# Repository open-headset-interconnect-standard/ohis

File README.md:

# Open-Headset-Interconnect-Standard

An open standard for a common interconnect between headsets and radios.

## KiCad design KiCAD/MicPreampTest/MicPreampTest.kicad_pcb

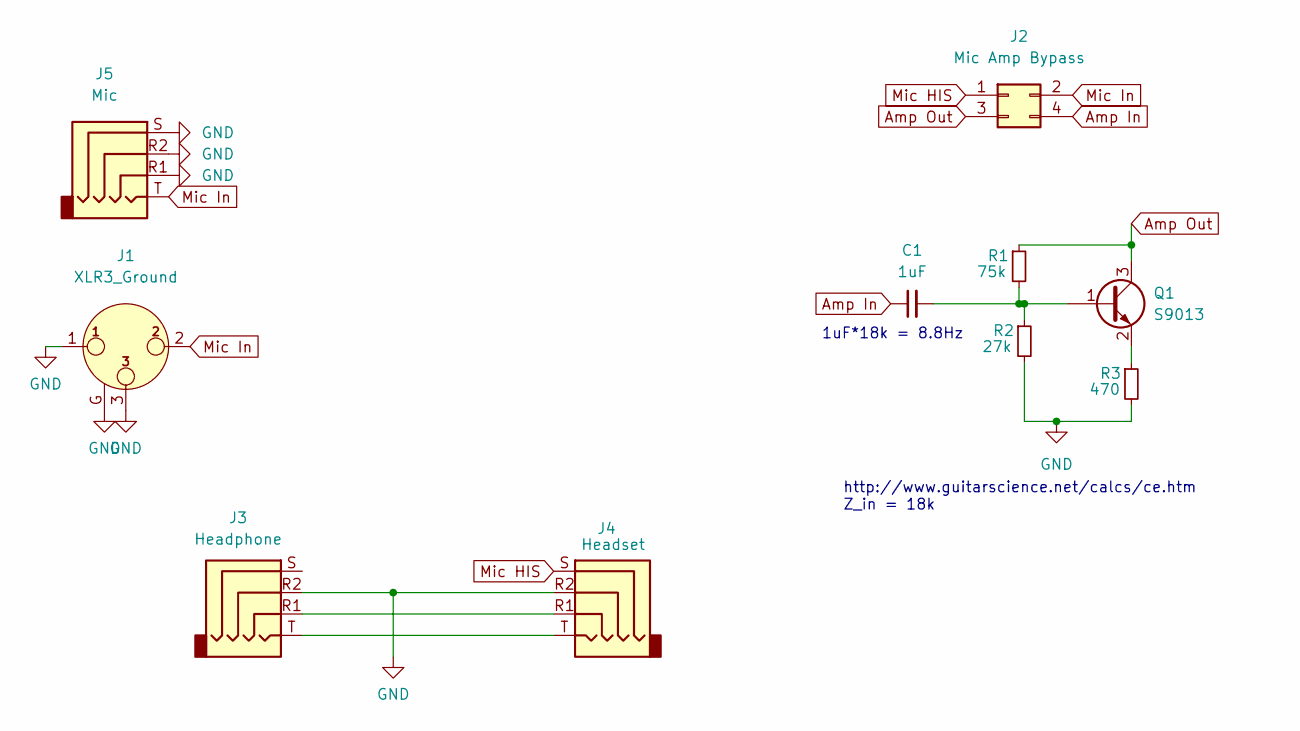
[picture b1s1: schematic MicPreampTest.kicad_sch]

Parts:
C1: 1uF; C_0603_1608Metric_Pad1.08x0.95mm_HandSolder; LCSC C15849
J1: XLR3_Ground; Jack_XLR_Neutrik_NC3FAAV2-0_Vertical
J2: Mic Amp Bypass; PinHeader_2x02_P2.54mm_Vertical
J3: Headphone; Conn-3.5mm-TRRS-PJ-320L
J4: Headset; Conn-3.5mm-TRRS-PJ-320L
J5: Mic; Conn-3.5mm-TRRS-PJ-320L
Q1: S9013; SOT-23; LCSC C6749
R1: 75k; R_0603_1608Metric_Pad0.98x0.95mm_HandSolder; LCSC C23242
R2: 27k; R_0603_1608Metric_Pad0.98x0.95mm_HandSolder; LCSC C22967
R3: 470; R_0603_1608Metric_Pad0.98x0.95mm_HandSolder; LCSC C23179

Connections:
Amp In: C1.1, J2.4
Amp Out: J2.3, Q1.3 (C), R1.1
GND: J1.1, J1.3, J1.G, J3.R2, J4.R2, J5.R1, J5.R2, J5.S, R2.2, R3.2
Mic HIS: J2.1, J4.S
Mic In: J1.2, J2.2, J5.T
unnamed: C1.2, Q1.1 (B), R1.2, R2.1
unnamed: J3.R1, J4.R1
unnamed: J3.T, J4.T
unnamed: Q1.2 (E), R3.1

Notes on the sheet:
http://www.guitarscience.net/calcs/ce.htm Z_in = 18k
1uF*18k = 8.8Hz

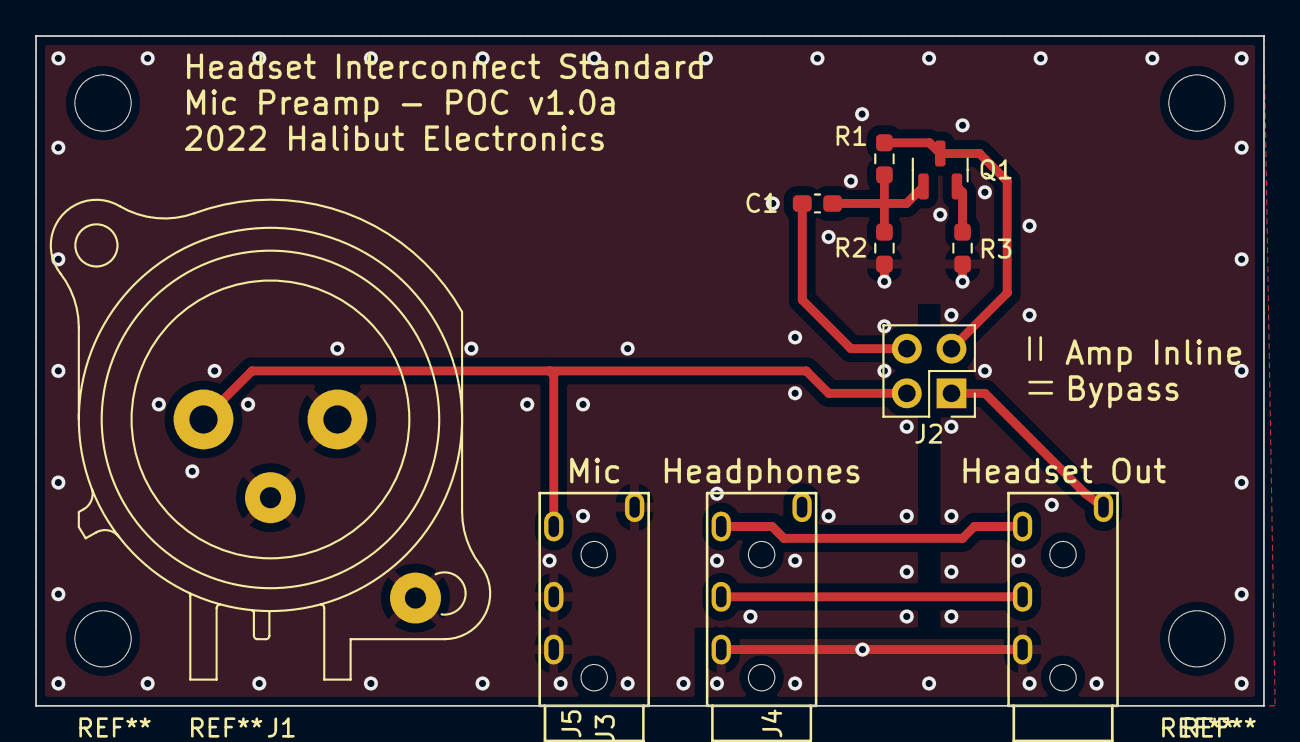
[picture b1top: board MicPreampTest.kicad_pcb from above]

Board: 2 copper layers, 69.9 x 38.1 mm, 10 parts (0 on the bottom side), 9 nets.

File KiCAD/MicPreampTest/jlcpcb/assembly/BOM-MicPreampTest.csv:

Comment,Designator,Footprint,LCSC
1uF,C1,C_0603_1608Metric_Pad1.08x0.95mm_HandSolder,C15849
27k,R2,R_0603_1608Metric_Pad0.98x0.95mm_HandSolder,C22967
470,R3,R_0603_1608Metric_Pad0.98x0.95mm_HandSolder,C23179
75k,R1,R_0603_1608Metric_Pad0.98x0.95mm_HandSolder,C23242
S9013,Q1,SOT-23,C6749

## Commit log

2022-07-11 Setting license to CC-BY-NC 4.0
2022-08-13 Rename to OPEN Headset Interconnect Standard
2022-08-25 https://github.com/Halibut-Electronics/Open-Headset-Interconnect-Standard/issues/1 Started working on the Standard doc. Setup for PDF autogeneration. KiCAD project for drawing things, 'cuz I've got a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
2022-08-25 Removed some yellow squiggly lines from the Markdown source
2022-08-25 Working on Section 3, "Why?"
2022-08-26 https://github.com/Halibut-Electronics/Open-Headset-Interconnect-Standard/issues/3 Moved KiCAD files from private repo.
2022-08-26 Added example link to PJ320A 4-pin TRRS sockets used on the board.
2022-08-26 https://github.com/Halibut-Electronics/Open-Headset-Interconnect-Standard/issues/3 Adding Dynamic Mic Preamp circuit.
2022-08-26 https://github.com/Halibut-Electronics/Open-Headset-Interconnect-Standard/issues/1 More work on the doc.
2022-08-26 Gave the TOC its own section.
2022-08-26 Cleaned a few things up. Fix link to Audio recording.
2022-08-27 Copying the actual recording instead of sym-linking.
2022-08-27 Updating link to recording.
2022-08-27 Page break.
2022-08-27 Links to email addresses.
2022-08-27 Formatting in Contributers
2022-08-31 First draft of QSO Today Expo presentation.
2022-08-31 Added QSO Today slides PDF to docs for publication.
2022-08-31 A few minor changes. Moved PDF to docs/ to avoid confusion.
2022-09-12 This is as recorded for the QSO Today Expo 2022-09
2023-01-11 Early versions of an OHIS logo. Not solidified yet. I'll add KiCAD files too.
2023-01-11 Not sure what changed. It's minor.
2023-05-02 Creating generic slide show. Added Overview diagram.
2023-05-16 Flyers created for Hamvention 2023
2023-05-16 Updated the slides for 2023 Hamvention
2023-05-16 https://github.com/open-headset-interconnect-standard/ohis/issues/10 Quick update before 2023 Hamvention
2023-05-16 Fix header numbering and TOC
2024-01-27 Update Open-Headset-Interconnect-Standard.md
    spelling
2024-03-18 Converted presentation slides to PPTX for IDXC 2024.
2024-07-03 Fix MP3 link in Appendix
2024-09-25 Work on the OHIS Logo
2024-09-25 A bit of clean up to the slides
2024-09-25 Removed a page break
2024-11-05 vectorized and responsive version
2024-11-19 Work on logo for a few things. STICKERS! @pbraun42
